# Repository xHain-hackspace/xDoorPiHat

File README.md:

# xDoorPiHat

Schematics and Boardfiles for PiHat that opens and closes the xDoor

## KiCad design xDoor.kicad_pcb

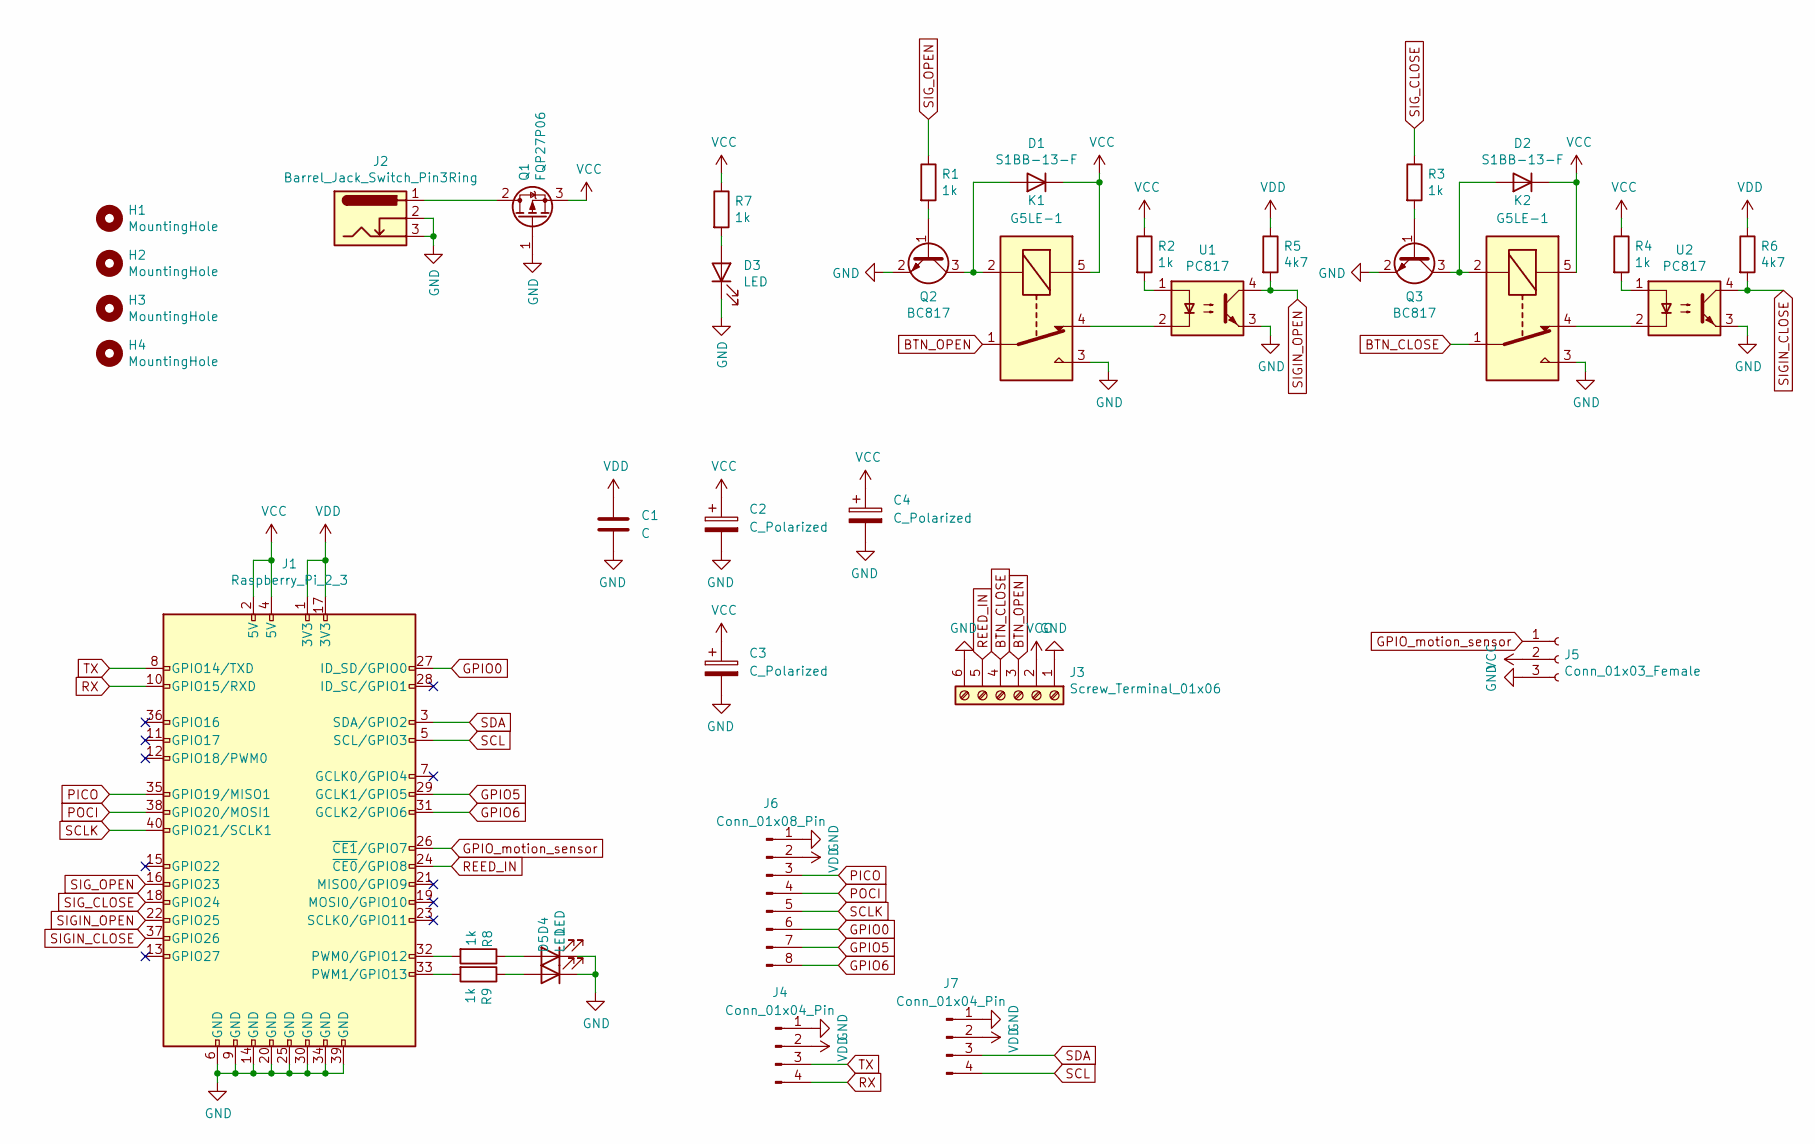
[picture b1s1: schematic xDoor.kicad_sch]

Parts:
C1: C; C_Disc_D6.0mm_W4.4mm_P5.00mm
C2, C3, C4: C_Polarized; CP_Radial_D8.0mm_P3.50mm
D1, D2: S1BB-13-F; D_SMB_Handsoldering; mouser 621-RS1BB-13-F
D3: LED; LED_1206_3216Metric_Pad1.42x1.75mm_HandSolder; mouser 859-LTST-C230GKT
D4: LED; LED_1206_3216Metric_Pad1.42x1.75mm_HandSolder; mouser 859-LTST-C150EKT
D5: LED; LED_1206_3216Metric_Pad1.42x1.75mm_HandSolder; mouser 859-LTST-C250TBKT
H1, H2, H3, H4: MountingHole; MountingHole_2.7mm_M2.5_DIN965
J1: Raspberry_Pi_2_3; PinSocket_2x20_P2.54mm_Vertical
J2: Barrel_Jack_Switch_Pin3Ring; BarrelJack_Horizontal
J3: Screw_Terminal_01x06; TerminalBlock_bornier-6_P5.08mm; mouser 490-TB006-508-06BE
J4, J7: Conn_01x04_Pin; PinHeader_1x04_P2.54mm_Vertical
J5: Conn_01x03_Female; PinSocket_1x03_P2.54mm_Vertical
J6: Conn_01x08_Pin; PinHeader_1x08_P2.54mm_Vertical
K1, K2: G5LE-1; Relay_SPDT_Omron-G5LE-1
Q1: FQP27P06; TO-263-2; mouser 512-FQP27P06
Q2, Q3: BC817; SOT-23; mouser 637-BC817-25
R1, R2, R3, R4, R7, R8, R9: 1k; R_1206_3216Metric_Pad1.30x1.75mm_HandSolder; mouser 279-CRGCQ1206F1K0
R5, R6: 4k7; R_1206_3216Metric_Pad1.30x1.75mm_HandSolder; mouser 791-WR12X4701FTL
U1, U2: PC817; DIP-4_W7.62mm; mouser 621-DPC817D-A-TU

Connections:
BTN_CLOSE: J3.4, K2.1
BTN_OPEN: J3.3, K1.1
GND: C1.2, C2.2, C3.2, C4.2, D3.1 (K), D4.1 (K), D5.1 (K), J1.6 (GND), J1.9 (GND), J1.14 (GND), J1.20 (GND), J1.25 (GND), J1.30 (GND), J1.34 (GND), J1.39 (GND), J2.2, J2.3, J3.1, J3.6, J4.1, J5.3, J6.1, J7.1, K1.3, K2.3, Q1.1 (G), Q2.2 (E), Q3.2 (E), U1.3, U2.3
GPIO0: J1.27 (ID_SD/GPIO0), J6.6
GPIO5: J1.29 (GCLK1/GPIO5), J6.7
GPIO6: J1.31 (GCLK2/GPIO6), J6.8
GPIO_motion_sensor: J1.26 (~CE1/GPIO7), J5.1
unnamed: D1.2 (A), K1.2, Q2.3 (C)
unnamed: D2.2 (A), K2.2, Q3.3 (C)
unnamed: D3.2 (A), R7.2
unnamed: D4.2 (A), R8.1
unnamed: D5.2 (A), R9.1
unnamed: J1.32 (PWM0/GPIO12), R8.2
unnamed: J1.33 (PWM1/GPIO13), R9.2
unnamed: K1.4, U1.2
unnamed: K2.4, U2.2
unnamed: J2.1, Q1.2 (D)
unnamed: Q2.1 (B), R1.2
unnamed: Q3.1 (B), R3.2
unnamed: R2.2, U1.1
unnamed: R4.2, U2.1
PICO: J1.35 (GPIO19/MISO1), J6.3
POCI: J1.38 (GPIO20/MOSI1), J6.4
REED_IN: J1.24 (~CE0/GPIO8), J3.5
RX: J1.10 (GPIO15/RXD), J4.4
SCL: J1.5 (SCL/GPIO3), J7.4
SCLK: J1.40 (GPIO21/SCLK1), J6.5
SDA: J1.3 (SDA/GPIO2), J7.3
SIGIN_CLOSE: J1.37 (GPIO26), R6.2, U2.4
SIGIN_OPEN: J1.22 (GPIO25), R5.2, U1.4
SIG_CLOSE: J1.18 (GPIO24), R3.1
SIG_OPEN: J1.16 (GPIO23), R1.1
TX: J1.8 (GPIO14/TXD), J4.3
VCC: C2.1, C3.1, C4.1, D1.1 (K), D2.1 (K), J1.2 (5V), J1.4 (5V), J3.2, J5.2, K1.5, K2.5, Q1.3 (S), R2.1, R4.1, R7.1
VDD: C1.1, J1.1 (3V3), J1.17 (3V3), J4.2, J6.2, J7.2, R5.1, R6.1

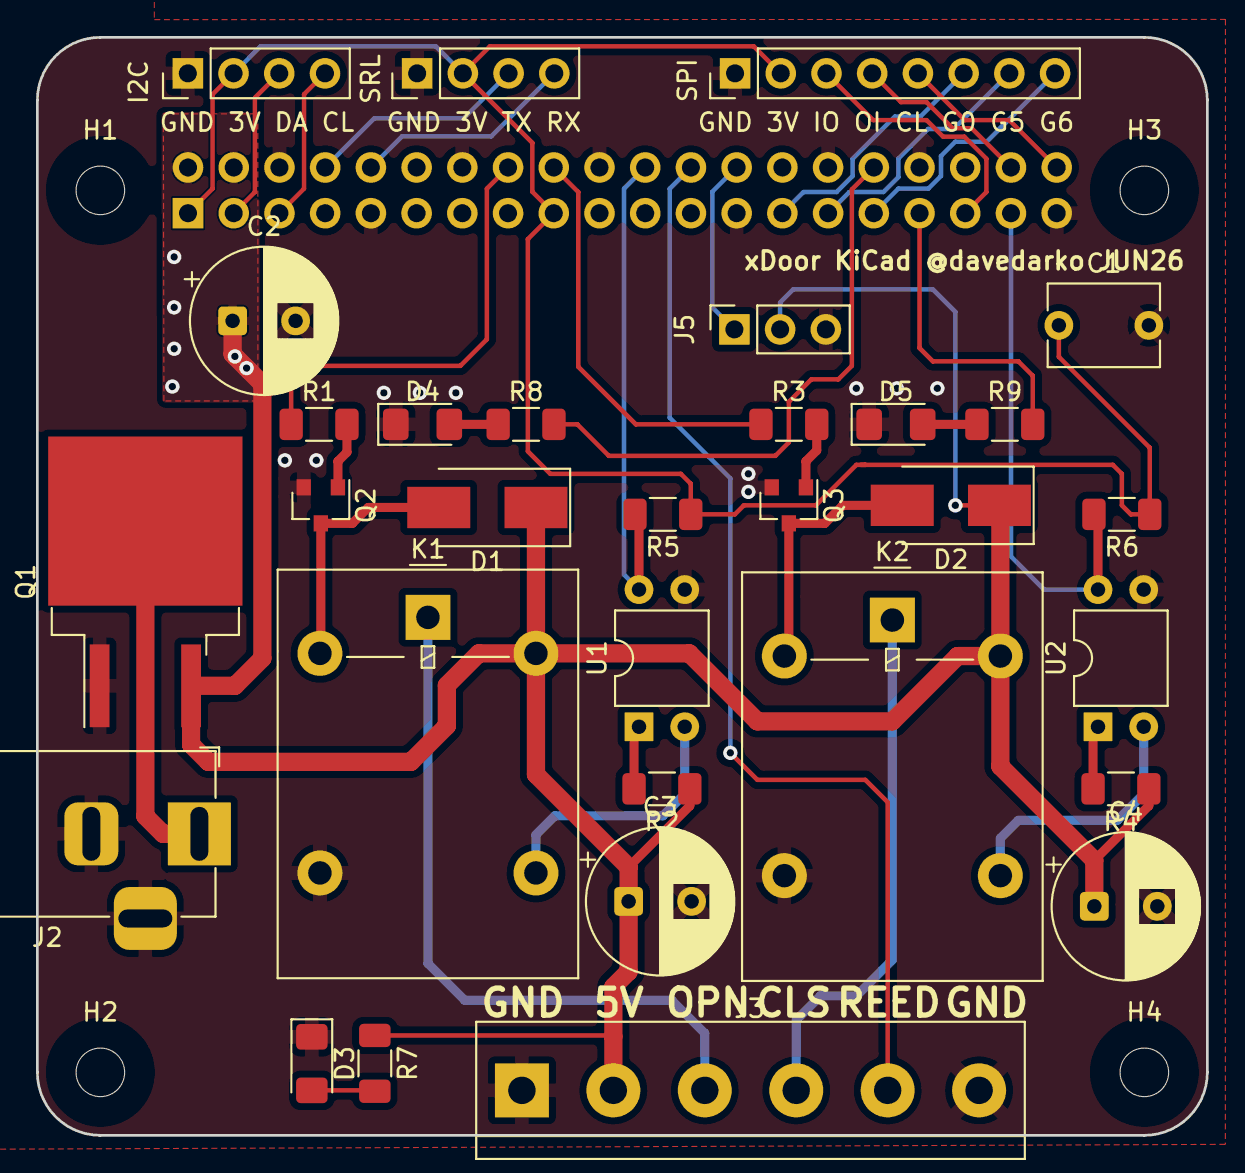
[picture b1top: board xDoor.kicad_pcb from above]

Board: 2 copper layers, 65.0 x 61.0 mm, 36 parts (1 on the bottom side), 35 nets.

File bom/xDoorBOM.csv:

"Id";"Designator";"Footprint";"Quantity";"Designation";"Supplier and ref";
1;"D4,D5,D3";"LED_1206_3216Metric_Pad1.42x1.75mm_HandSolder";3;"LED";;;
2;"R5,R6";"R_1206_3216Metric_Pad1.30x1.75mm_HandSolder";2;"4k7";;;
3;"R7,R1,R2,R3,R4,R8,R9";"R_1206_3216Metric_Pad1.30x1.75mm_HandSolder";7;"1k";;;
4;"H1,H2,H3,H4";"MountingHole_2.7mm_M2.5_DIN965";4;"MountingHole";;;
5;"J4";"JST_SH_SM04B-SRSS-TB_1x04-1MP_P1.00mm_Horizontal";1;"Conn_01x04_Female";;;
6;"J2";"BarrelJack_Horizontal";1;"Barrel_Jack_Switch_Pin3Ring";;;
7;"K1,K2";"Relay_SPDT_Omron_G5V-1";2;"G5V-1";;;
8;"Q1";"TO-263-2";1;"FQP27P06";;;
9;"D1,D2";"D_SMB_Handsoldering";2;"S1BB-13-F";;;
10;"Q2,Q3";"SOT-23";2;"BC817";;;
11;"U1,U2";"DIP-4_W7.62mm";2;"PC817";;;
12;"J5";"PinSocket_1x03_P2.54mm_Vertical";1;"Conn_01x03_Female";;;
13;"J3";"TerminalBlock_bornier-6_P5.08mm";1;"Screw_Terminal_01x06";;;
14;"J1";"PinSocket_2x20_P2.54mm_Vertical";1;"Raspberry_Pi_2_3";;;

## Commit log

2022-10-04 adding all current files
2023-04-24 added bom info
2023-04-24 why would I exclude BOMs
2023-04-24 ok bom
2026-06-07 different servos, more caps
